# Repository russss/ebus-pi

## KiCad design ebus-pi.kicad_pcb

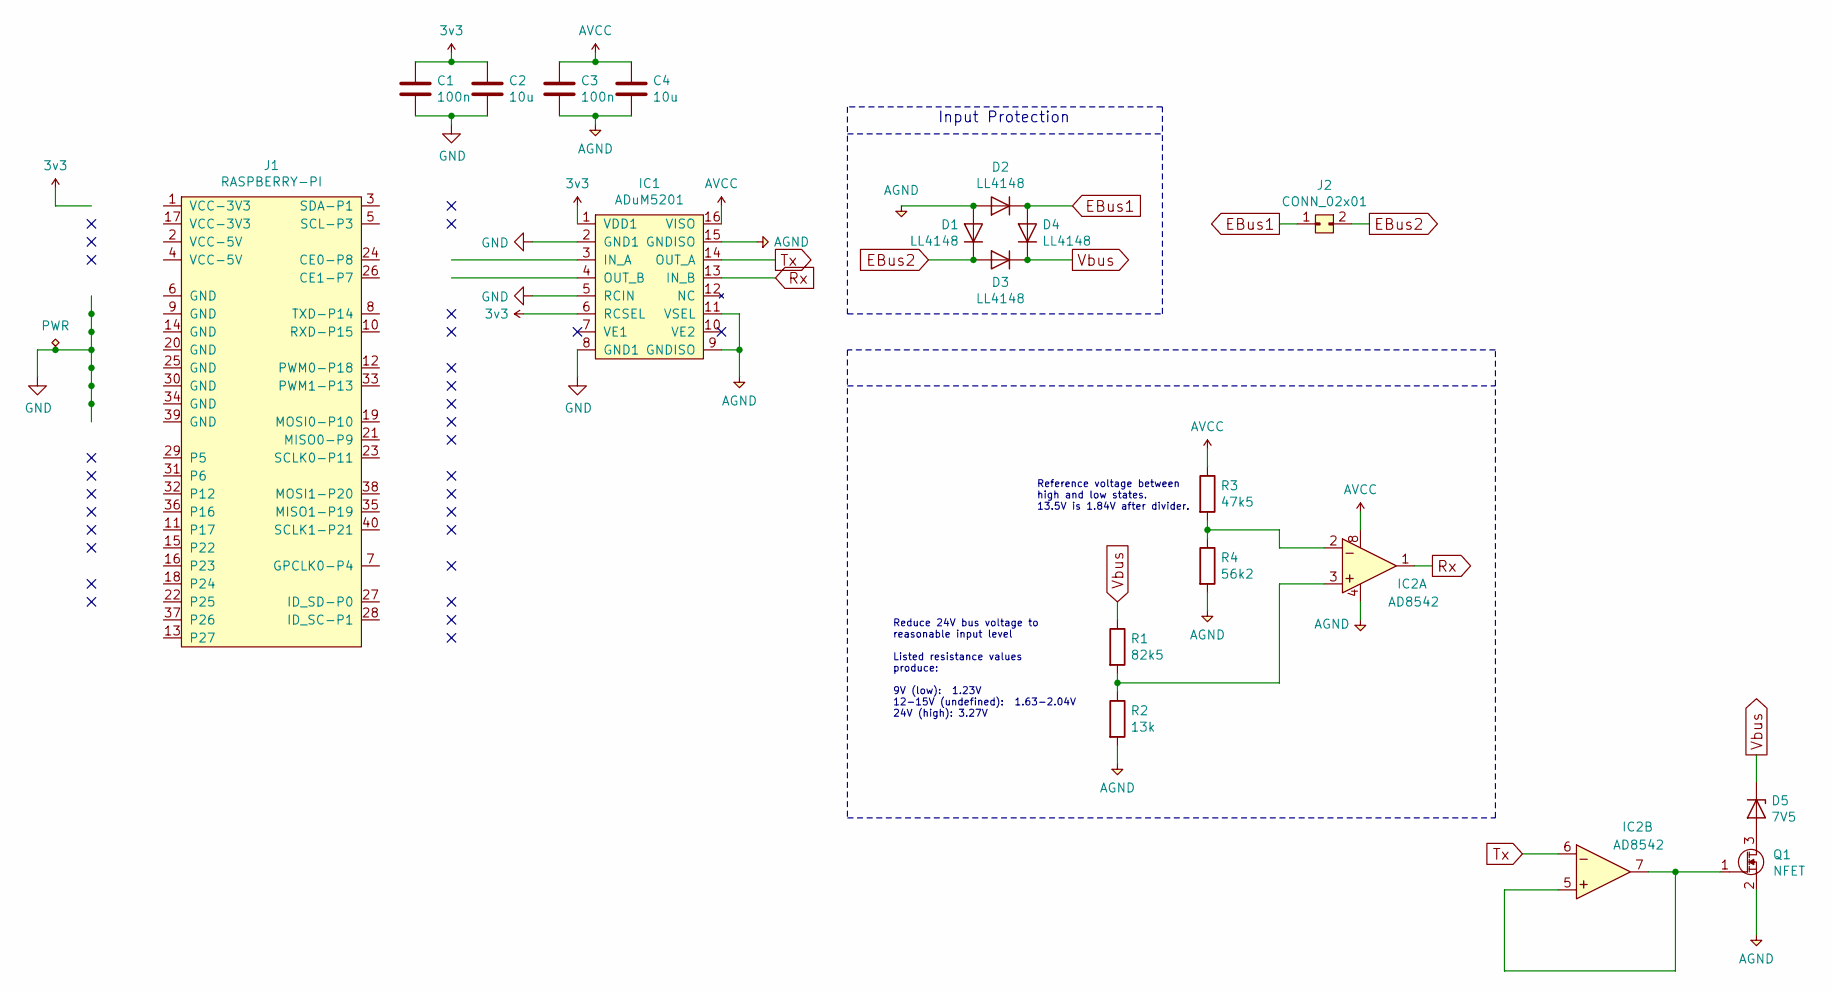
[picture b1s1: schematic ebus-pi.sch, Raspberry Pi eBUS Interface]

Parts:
C1, C3: 100n; 0805
C2, C4: 10u; 0805
D1, D2, D3, D4: LL4148; SOD-123
D5: 7V5; SOD-123
IC1: ADuM5201; SOIC-16-W; Farnell 2067773
IC2: AD8542; MSOP-8; Farnell 2305609
J1: RASPBERRY-PI; Pin_Header_Straight_2x20_Pitch2.54mm
J2: CONN_02x01; MSTBVA2,5-2
Q1: NFET; SOT-23
R1: 82k5; 0805
R2: 13k; 0805
R3: 47k5; 0805
R4: 56k2; 0805

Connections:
3v3: C1.1, C2.1, IC1.1 (VDD1), IC1.6 (RCSEL), J1.1 (VCC-3V3)
AGND: C3.2, C4.2, D1.2 (A), D2.2 (A), IC1.9 (GNDISO), IC1.11 (VSEL), IC1.15 (GNDISO), IC2.4 (V-), Q1.2 (S), R2.2, R4.2
AVCC: C3.1, C4.1, IC1.16 (VISO), IC2.8 (V+), R3.1
EBus1: D2.1 (K), D4.2 (A), J2.1
EBus2: D1.1 (K), D3.2 (A), J2.2
GND: C1.2, C2.2, IC1.2 (GND1), IC1.5 (RCIN), IC1.8 (GND1), J1.6 (GND), J1.9 (GND), J1.14 (GND), J1.20 (GND), J1.25 (GND), J1.30 (GND), J1.34 (GND), J1.39 (GND)
unnamed: D5.2 (A), Q1.3 (D)
unnamed: IC1.3 (IN_A), J1.8 (TXD-P14)
unnamed: IC1.4 (OUT_B), J1.10 (RXD-P15)
unnamed: IC2.2 (-A), R3.2, R4.1
unnamed: IC2.3 (+A), R1.2, R2.1
unnamed: IC2.5 (+B), IC2.7 (OUTB), Q1.1 (G)
Rx: IC1.13 (IN_B), IC2.1 (OUTA)
Tx: IC1.14 (OUT_A), IC2.6 (-B)
Vbus: D3.1 (K), D4.1 (K), D5.1 (K), R1.1

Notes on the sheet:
Reduce 24V bus voltage to reasonable input level Listed resistance values produce: 9V (low): 1.23V 12-15V (undefined): 1.63-2.04V 24V (high): 3.27V
Reference voltage between high and low states. 13.5V is 1.84V after divider.
Input Protection

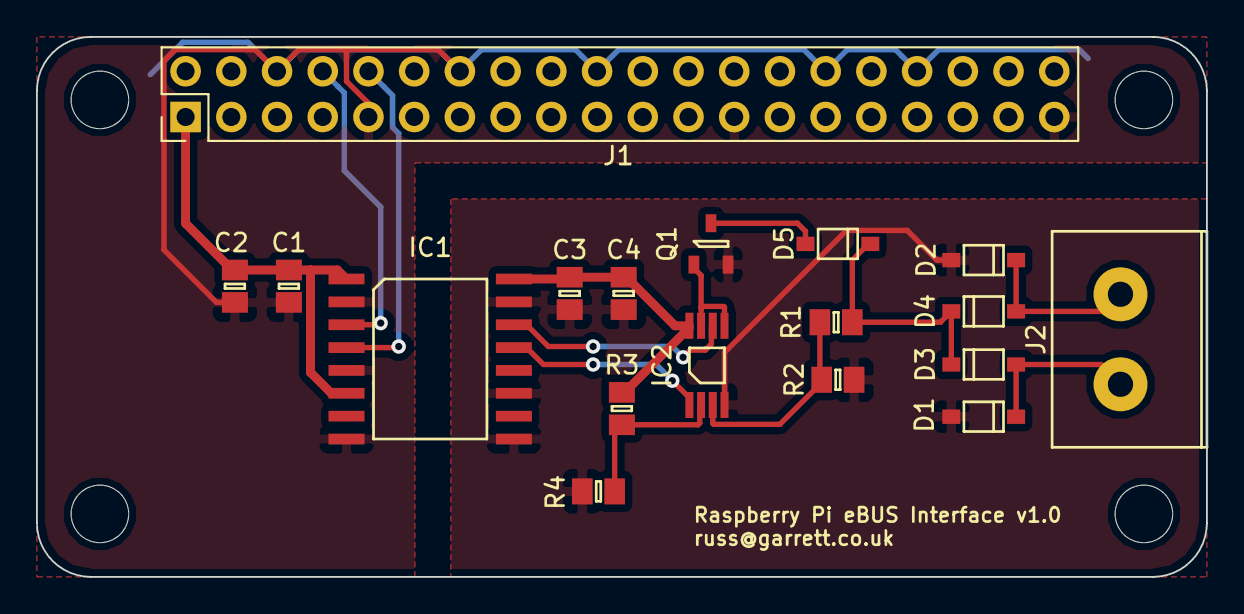
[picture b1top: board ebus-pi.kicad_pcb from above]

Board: 2 copper layers, 65.0 x 30.0 mm, 18 parts (0 on the bottom side), 15 nets.

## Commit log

2017-04-28 Version 1.0
